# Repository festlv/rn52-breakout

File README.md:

RN52 breakout board
=======================

KiCad schematics, library symbol and footprints for RN52 Bluetooth module.

The following functionality is broken out:
* UART's RX/TX pins
* GPIO9 (command/data mode selection)
* GPIO7 (UART baud rate selection)
* GPIO4 (factory reset switch)
* PWREN (enable power)
* LED0, LED1
* Audio output, in a really, really dumb way. You should use amplifier with differential input.

Be warned- the PCB was designed for parts I had on hand and home-made production 
process (single layer, fat tracks).

I had wrong footprint for linear regulator at the first try- it's now been
fixed in master.

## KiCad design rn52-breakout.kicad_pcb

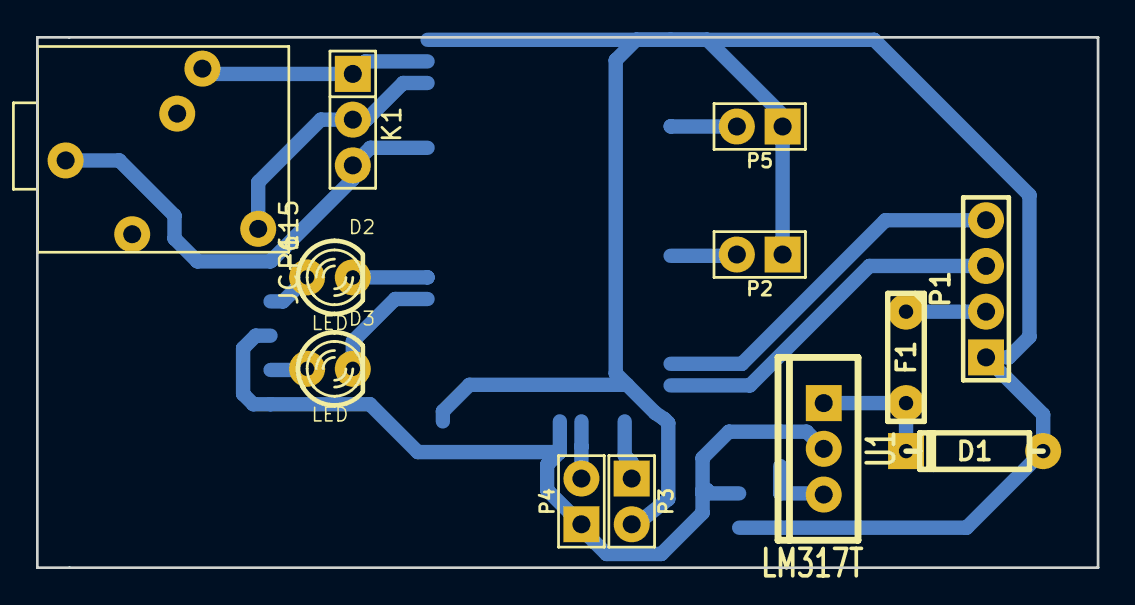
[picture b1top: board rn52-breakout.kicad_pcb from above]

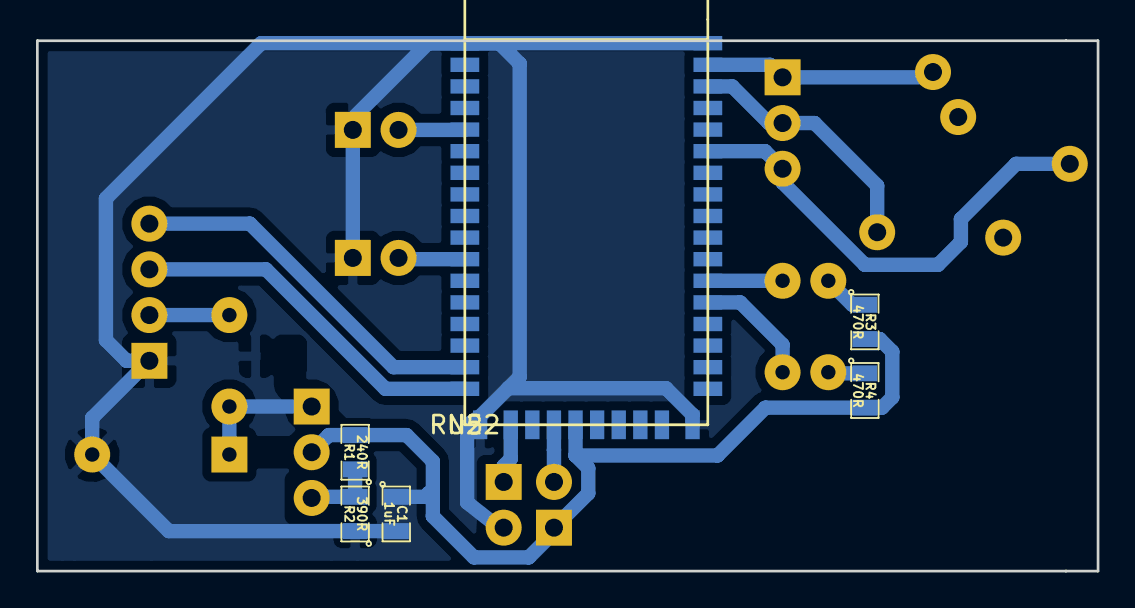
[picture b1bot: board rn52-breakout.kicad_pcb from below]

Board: 2 copper layers, 58.9 x 29.5 mm, 18 parts (6 on the bottom side), 18 nets.

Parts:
C1: 1uF; SM0805
D1: DIODE; D3
D2, D3: LED; LED-3MM
F1: FUSE; C2
K1: CONN_3; PIN_ARRAY_3X1
P1: UART; PIN_ARRAY_4x1
P2: MODE_SET; PIN_ARRAY_2X1
P3: BAUD_SET; PIN_ARRAY_2X1
P4: PWREN; PIN_ARRAY_2X1
P5: FACTORY; PIN_ARRAY_2X1
P6: JC-115
R1: 240R; SM0805
R2: 390R; SM0805
R3, R4: 470R; SM0805
U1: LM317T; TO220_VERT
U2: RN52

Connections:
+3.3V: C1.1, P4.1, R1.2, R3.2, R4.2, U1.2, U2.22
+5V: F1.1, P1.2
GND: C1.2, D1.1, P1.1, P2.1, P3.2, P5.1, R2.1, U2.1, U2.18, U2.27, U2.44
unnamed: P2.2, U2.11
unnamed: P3.1, U2.19
unnamed: R1.1, R2.2, U1.1
unnamed: D1.2, F1.2, U1.3
unnamed: K1.3, P6.5, U2.39
unnamed: K1.2, P6.1, U2.42
unnamed: K1.1, P6.3, U2.43
unnamed: D2.2, U2.33
unnamed: D3.2, U2.32
unnamed: D3.1, R4.1
unnamed: P5.2, U2.5
unnamed: P1.4, U2.16
unnamed: P4.2, U2.21
unnamed: D2.1, R3.1
unnamed: P1.3, U2.17

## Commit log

2014-04-24 Pre-production version, still need a footprint for audio connector
2014-04-24 Formatting changes in readme
2014-04-24 Added PDF version of schematics
2014-04-25 Added 3.5mm jack connector
2014-04-25 Updated schematic in PDF format
2014-04-27 Fixed incorrect pinout for lin. regul., added some vanity pictures
